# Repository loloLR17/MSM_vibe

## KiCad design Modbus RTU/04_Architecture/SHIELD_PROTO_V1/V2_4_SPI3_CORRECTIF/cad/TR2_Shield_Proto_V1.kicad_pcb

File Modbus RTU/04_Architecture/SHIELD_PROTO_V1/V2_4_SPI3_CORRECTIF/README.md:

# Shield V2.4 électrique — SPI3 corrigé, CANDIDAT NON LIBÉRÉ

Mission `TR2-20261118-SHIELD-V24-SPI3-GERBER-CORRECTIF`, départ `fb7167548dc1f55eb8250d3d52c8c85dd5caa8c9`. Cette variante distincte corrige uniquement les six contacts J8 concernés et les pistes SPI3 nécessaires. Aucun accès matériel, achat ou envoi au fabricant.

## Fichiers à revoir

- [Projet KiCad](cad/TR2_Shield_Proto_V1.kicad_pro), [PCB](cad/TR2_Shield_Proto_V1.kicad_pcb), [schéma](cad/TR2_Shield_Proto_V1.kicad_sch), bibliothèques et routes locales dans `cad/`.
- [ZIP CAM candidat unique](exports/TR2_SHIELD_V24_SPI3_CANDIDAT_NON_LIBERE.zip), [SHA256 externe](exports/TR2_SHIELD_V24_SPI3_CANDIDAT_NON_LIBERE.zip.sha256), [inventaire de ses9membres](preuves/CAM-manifeste.json). Sept Gerber, deux Excellon ; plans PDF et gbrjob informatifs hors ZIP, aucun vieux CAM incorporé.
- [Schéma PDF natif](exports/schema.pdf), [implantation](exports/implantation.png), [cuivre avant](exports/cuivre-dessus.png), [cuivre arrière miroir](exports/cuivre-dessous-miroir.png), PDF/SVG vectoriels correspondants.
- [Contrôles E-01/M-01](CONTROLES_ET_LIMITES.md), [180contacts](preuves/E01/MATRICE_E01_180_CONTACTS.csv), [17nets](preuves/E01/MATRICE_E01_17_NETS.csv), [diff V2.3/V2.4](preuves/diff-V23-V24.json).
- [Achats urgents mis à jour avec le stock utilisateur](achats/ACHATS_URGENTS.md), [BOMnative](achats/BOM_NATIVE_2_SHIELDS.csv), [liste de préparation](achats/PREPARATION_2_SHIELDS.csv).

La [relecture distante intégrale](preuves/publication-first-readback.json) porte sur les fichiers et les neuf membres du ZIP réellement récupérés depuis GitHub ; elle ne vaut pas libération de fabrication.

## Correction explicite

| Net MCU conservé | V2.3 fautive | V2.4 | Fonction constructeur |
|---|---:|---:|---|
| PC9 / ACC_CS |J8-21|**J8-19**|CS|
| PC10 / ACC_SCK |J8-22|**J8-20**|SCL|
| PC12 / ACC_MOSI |J8-23|**J8-21**|SDA|
| PC11 / ACC_MISO |J8-24|**J8-22**|SDO|
| NC |19/20|**23/24**|aucune connexion intentionnelle|

J8 ne bouge pas : mêmes24pads, entre-rangées15,24mm, même sens de numérotation. Broches1/2 alimentées3V3 et13GND inchangées. Les autres nets, notamment J9/LPUART/PG4/J5 physiquement qualifiés sur l'ancien assemblage001, sont conservés exactement. Les marquages natifs historiques V1.9/DRAFT et ARNACO restent intacts pour respecterM-01 ; l'identité électriqueV2.4 et le statut candidat sont portés par ce dossier/ZIP/manifest, pas par une modification de la sérigraphie.

**Résultat numérique :** ERC0/DRC0/non-connectés0/parité0 ; E-01 180PASS,17nets, zéro court-circuit/coupure géométrique dans les deux vrais cuivres exportés. M-01 :19empreintes/191géométries de pads-trous/4vias exactement conservés ;232fichiers historiques V2.3/V2.7 intacts ;191interfaces de perçage recoupées au STEP gelé. Huit mutations interdites rejetées par les contrôles négatifs en mémoire.

**Cela n'est pas un GO fabrication.** Le futur PCB V2.4 n'existe pas encore physiquement. Montage à froid, références réellement montées, insertion/tenue, soudures, rails, SPI3 et coexistence matérielle restent à qualifier. Le défaut des V2.3 existantes n'est pas réparé par la publication. Revue indépendante ChatGPT puis décision utilisateur requises avant toute diffusion au fabricant.

## Reproduction et environnement

KiCad Windows10.0.6 sous `C:/Program Files/KiCad/10.0/bin`, PythonLinux et modules déjà présents via `PYTHONPATH=/home/lolo/dev/msm/cache/shield-pylibs`. Pour STEP/CadQuery, Python `/home/lolo/dev/msm/cache/shield-v15-cad-venv/bin/python`. Aucune politique Windows modifiée.

Les générateurs sont destinés à une **copie de travail isolée avec toutes les modifications manuelles préservées**, pas à écraser ce lot figé. Ordre : `correct_spi3.py` (sourceV2.3 immutable), `route_spi3.py` (5branches terminales, sans via nouveau), `fill_candidate.py` avec PythonKiCad vers un fichier temporaire neuf, `merge_zone_fills.py` (seuls polygones de cuivre dérivés), `verify_m01.py`, `verify_v27_step.py`, ERC/DRC natifs, puis `export_design.py`. L'exporteur exige ces gates et refuse de mélanger des CAM déjà présents.

Commandes ERC/DRC réellement exécutées dans `docs/checks/native-commands.json`. Pour les preuves constructeur : `build_reference.py` (ne lit aucun projet), `read_native.py` avec PythonKiCad, `audit_orientations.py`, `verify_symbols.py`. Après `package_cam.py`, `audit_e01.py` lit le vrai ZIP/les deux cuivres et Excellon ; `compare_before_after.py`, `negative_m01_controls.py`, `verify_stock_options.py` complètent les contrôles. Les sources fabricant externes sont épinglées par URL/version/hash dans `preuves/E01/reference-constructeurs.json` ; conserver leurs caches `/home/lolo/dev/msm/reports/` pour une reproduction complète. Aucun original fabricant redistribué à tort comme création du projet.

Le gbrjob natif conserve une taille90,05×100,05mm incluant le trait de contour ; les axes du vrai contour restent90×100mm. Son `Finish:None` n'est pas une sélection de finition de commande. Les paramètres de fabrication et le paiement seront une décision distincte.

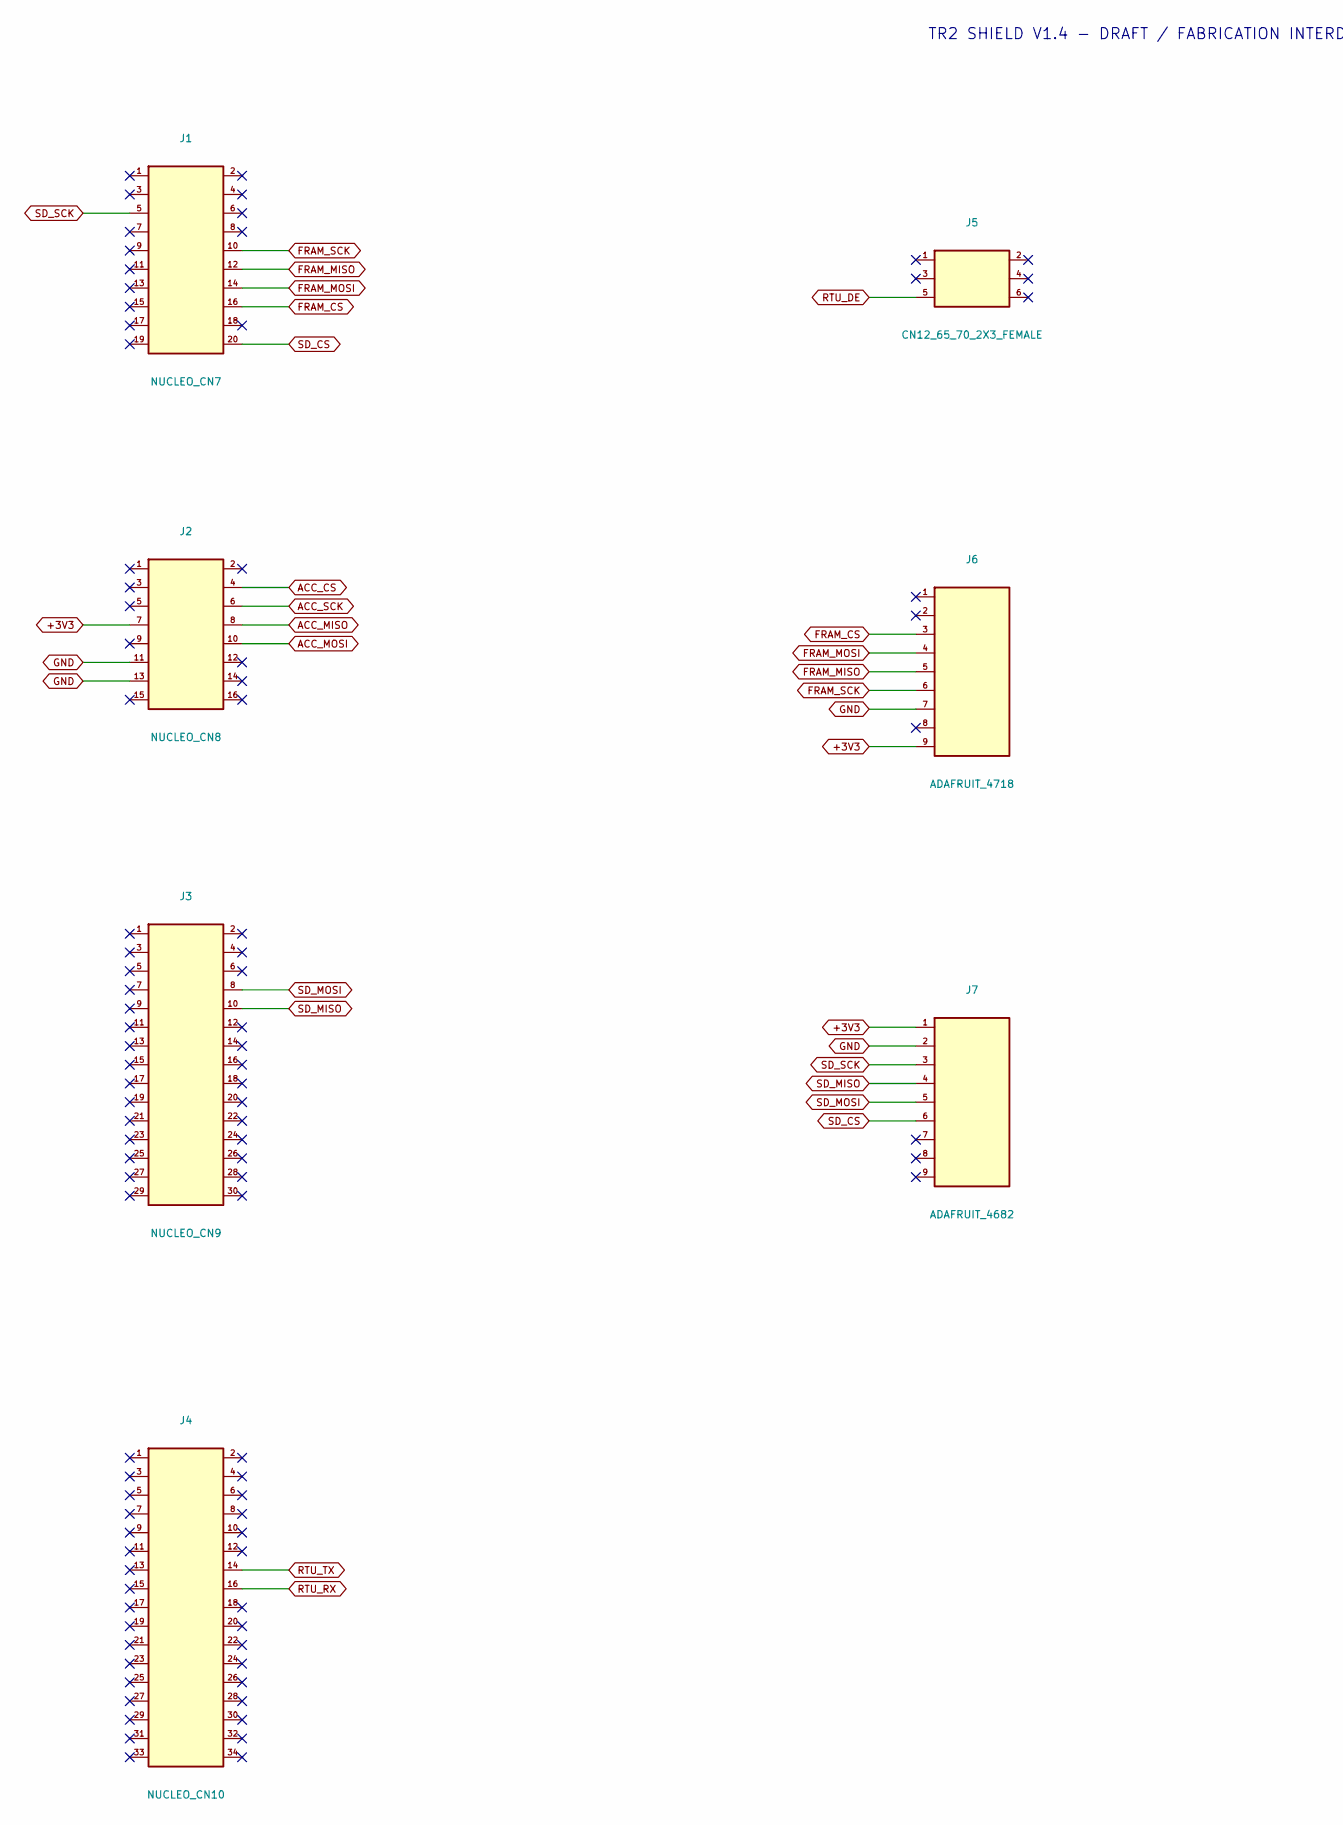
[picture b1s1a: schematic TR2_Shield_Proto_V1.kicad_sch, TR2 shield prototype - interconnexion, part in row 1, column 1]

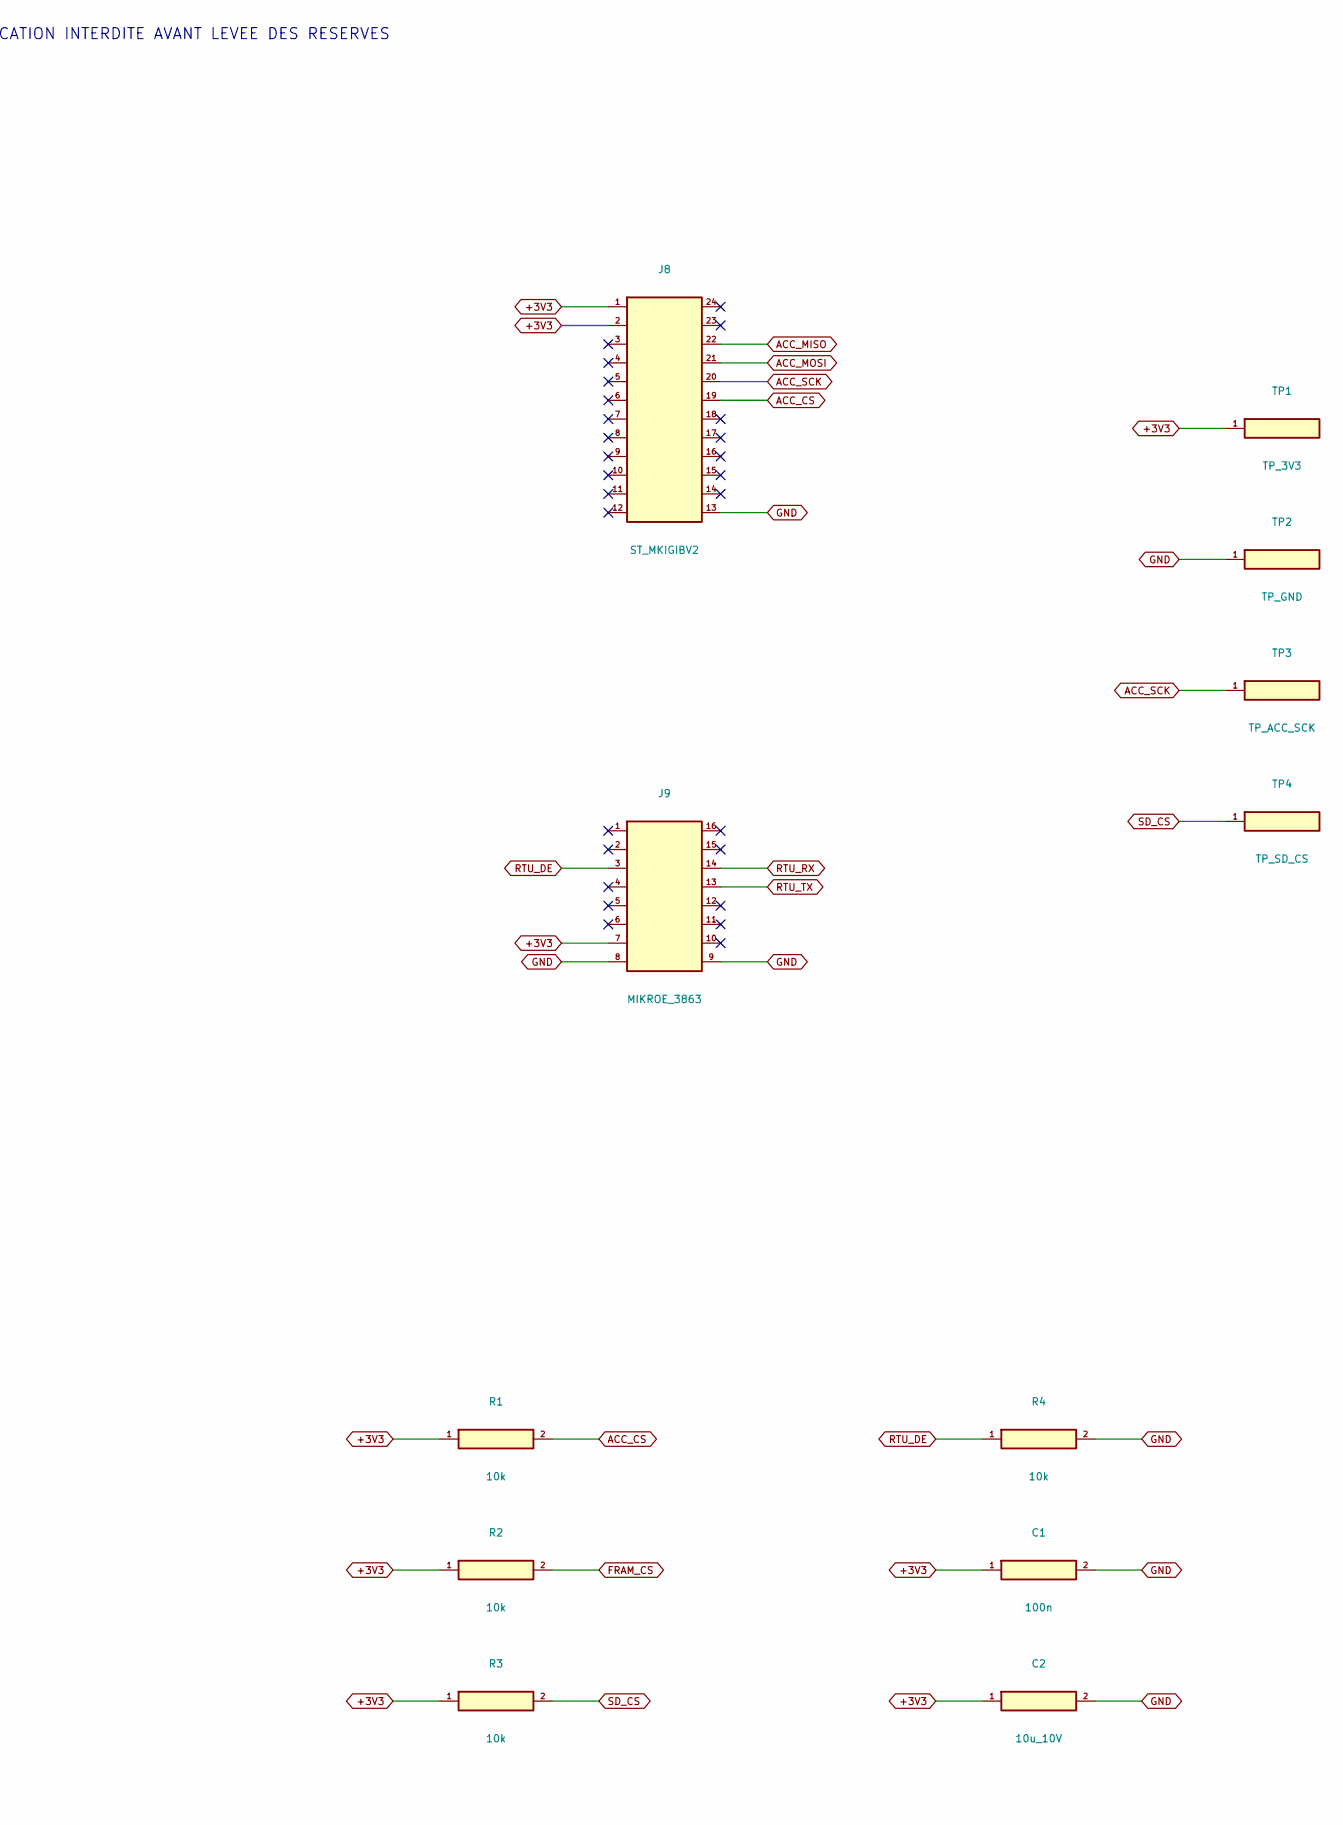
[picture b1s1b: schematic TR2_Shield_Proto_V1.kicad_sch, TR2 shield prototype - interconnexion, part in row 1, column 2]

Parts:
C1: 100n; C1_100n
C2: 10u_10V; C2_10u_10V
J1: NUCLEO_CN7; J1_NUCLEO_CN7
J2: NUCLEO_CN8; J2_NUCLEO_CN8
J3: NUCLEO_CN9; J3_NUCLEO_CN9
J4: NUCLEO_CN10; J4_NUCLEO_CN10
J5: CN12_65_70_2X3_FEMALE; J5_CN12_65_70_2X3_FEMALE
J6: ADAFRUIT_4718; J6_ADAFRUIT_4718
J7: ADAFRUIT_4682; J7_ADAFRUIT_4682
J8: ST_MKIGIBV2; J8_ST_MKIGIBV2
J9: MIKROE_3863; J9_MIKROE_3863
R1: 10k; R1_10k
R2: 10k; R2_10k
R3: 10k; R3_10k
R4: 10k; R4_10k
TP1: TP_3V3; TP1_TP_3V3
TP2: TP_GND; TP2_TP_GND
TP3: TP_ACC_SCK; TP3_TP_ACC_SCK
TP4: TP_SD_CS; TP4_TP_SD_CS

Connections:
+3V3: C1.1 (+3V3), C2.1 (+3V3), J2.7 (+3V3), J6.9 (+3V3), J7.1 (+3V3), J8.1 (+3V3), J8.2 (+3V3), J9.7 (+3V3), R1.1 (+3V3), R2.1 (+3V3), R3.1 (+3V3), TP1.1
ACC_CS: J2.4 (ACC_CS), J8.19 (CS), R1.2 (ACC_CS)
ACC_MISO: J2.8 (ACC_MISO), J8.22 (SDO)
ACC_MOSI: J2.10 (ACC_MOSI), J8.21 (SDA)
ACC_SCK: J2.6 (ACC_SCK), J8.20 (SCL), TP3.1
FRAM_CS: J1.16 (FRAM_CS), J6.3 (FRAM_CS), R2.2 (FRAM_CS)
FRAM_MISO: J1.12 (FRAM_MISO), J6.5 (FRAM_MISO)
FRAM_MOSI: J1.14 (FRAM_MOSI), J6.4 (FRAM_MOSI)
FRAM_SCK: J1.10 (FRAM_SCK), J6.6 (FRAM_SCK)
GND: C1.2 (GND), C2.2 (GND), J2.11 (GND), J2.13 (GND), J6.7 (GND), J7.2 (GND), J8.13 (GND), J9.8 (GND), J9.9 (GND), R4.2 (GND), TP2.1
RTU_DE: J5.5 (RTU_DE), J9.3 (RTU_DE), R4.1 (RTU_DE)
RTU_RX: J4.16 (RTU_RX), J9.14 (RTU_RX)
RTU_TX: J4.14 (RTU_TX), J9.13 (RTU_TX)
SD_CS: J1.20 (SD_CS), J7.6 (SD_CS), R3.2 (SD_CS), TP4.1
SD_MISO: J3.10 (SD_MISO), J7.4 (SD_MISO)
SD_MOSI: J3.8 (SD_MOSI), J7.5 (SD_MOSI)
SD_SCK: J1.5 (SD_SCK), J7.3 (SD_SCK)

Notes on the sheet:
TR2 SHIELD V1.4 - DRAFT / FABRICATION INTERDITE AVANT LEVEE DES RESERVES

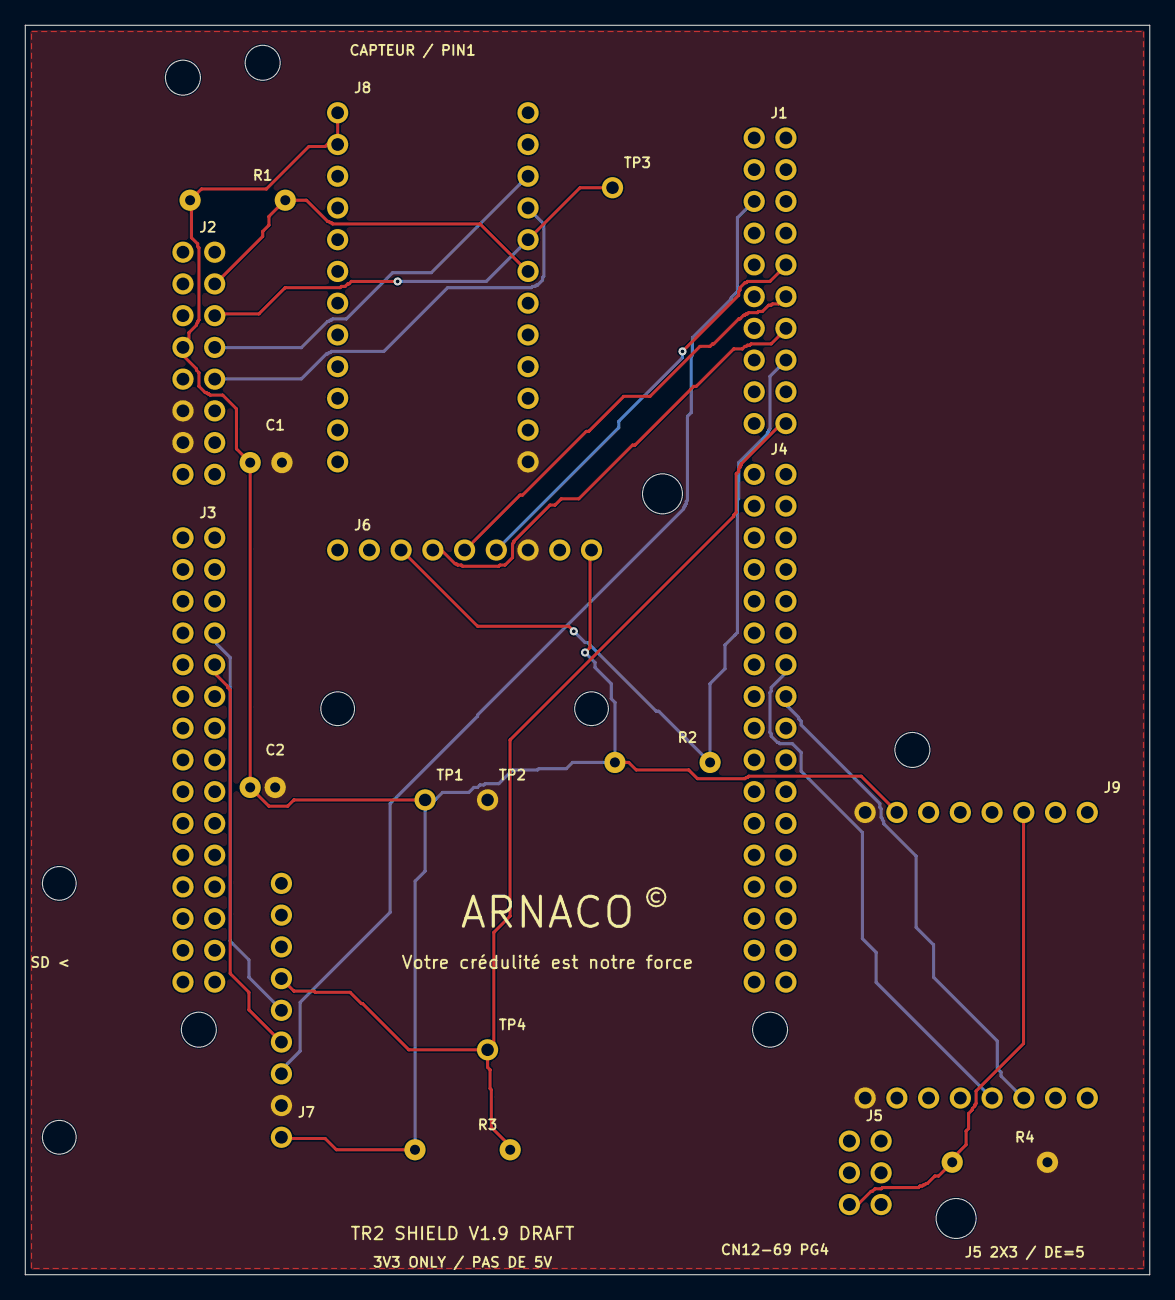
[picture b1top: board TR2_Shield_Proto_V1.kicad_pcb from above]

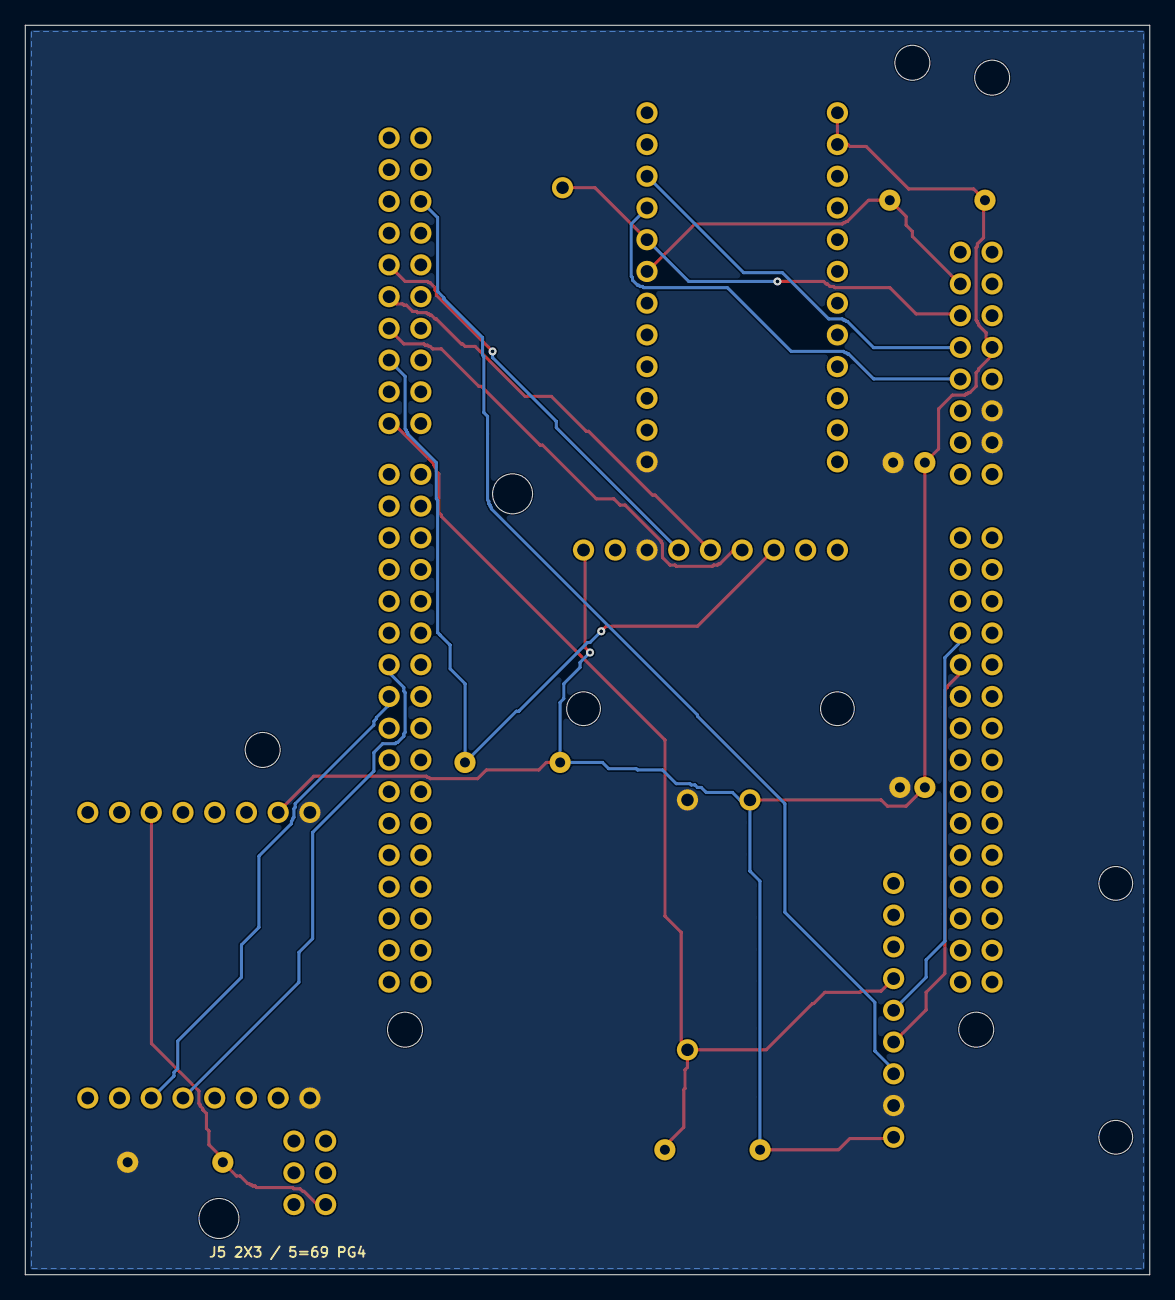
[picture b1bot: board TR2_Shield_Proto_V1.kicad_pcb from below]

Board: 2 copper layers, 90.0 x 100.0 mm, 19 parts (5 on the bottom side), 17 nets.
